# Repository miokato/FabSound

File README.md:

# FabSound
## This repository is created for people who want to make easy sound system using Arduino by yourself.

1. Amplifire
2. Speaker
3. Synthesizer

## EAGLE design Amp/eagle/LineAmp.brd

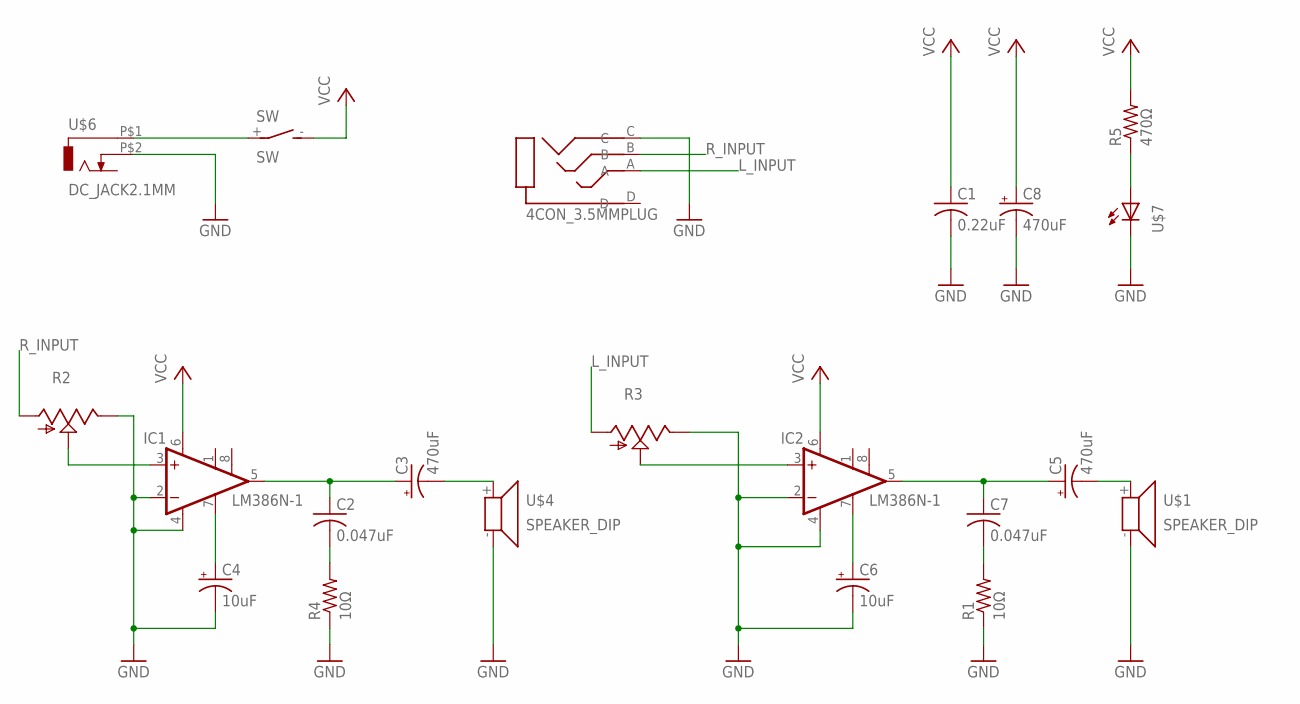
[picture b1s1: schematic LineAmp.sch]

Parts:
C1: 0.22uF; C075-042X103
C2, C7: 0.047uF; C050-024X044
C3, C5, C8: 470uF; E7,5-16
C4, C6: 10uF; E2-5
IC1, IC2: LM386N-1; DIL08
R1, R4: 10Ω; M1206
R2, R3: TRIM_US-ALPS-PANEL; ALPS-POT-PANEL
R5: 470Ω; M1206
SW: SW; 2PIN_DIP
U$1, U$4: SPEAKER_DIP; 2PIN_DIP
U$5: 4CON_3.5MMPLUG; 4PIN_DIP
U$6: DC_JACK2.1MM
U$7: LED5MM; 5MM

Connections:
GND: C1.2, C4.-, C6.-, C8.-, IC1.2 (-IN), IC1.4 (GND), IC2.2 (-IN), IC2.4 (GND), R1.1, R2.P$1 (E), R3.P$1 (E), R4.1, U$1.-, U$4.-, U$5.C, U$6.P$2 (2), U$7.OUT (C)
L_INPUT: R3.P$3 (A), U$5.A
unnamed: IC2.3 (+IN), R3.P$2 (S)
unnamed: C4.+, IC1.7 (BYPASS)
unnamed: IC1.3 (+IN), R2.P$2 (S)
unnamed: C6.+, IC2.7 (BYPASS)
unnamed: C2.1, C3.+, IC1.5 (OUT)
unnamed: C3.-, U$4.+
unnamed: C5.+, C7.1, IC2.5 (OUT)
unnamed: C5.-, U$1.+
unnamed: C2.2, R4.2
unnamed: C7.2, R1.2
unnamed: R5.1, U$7.IN (A)
unnamed: SW.+, U$6.P$1 (1)
R_INPUT: R2.P$3 (A), U$5.B
VCC: C1.1, C8.+, IC1.6 (VS), IC2.6 (VS), R5.2, SW.- (S)

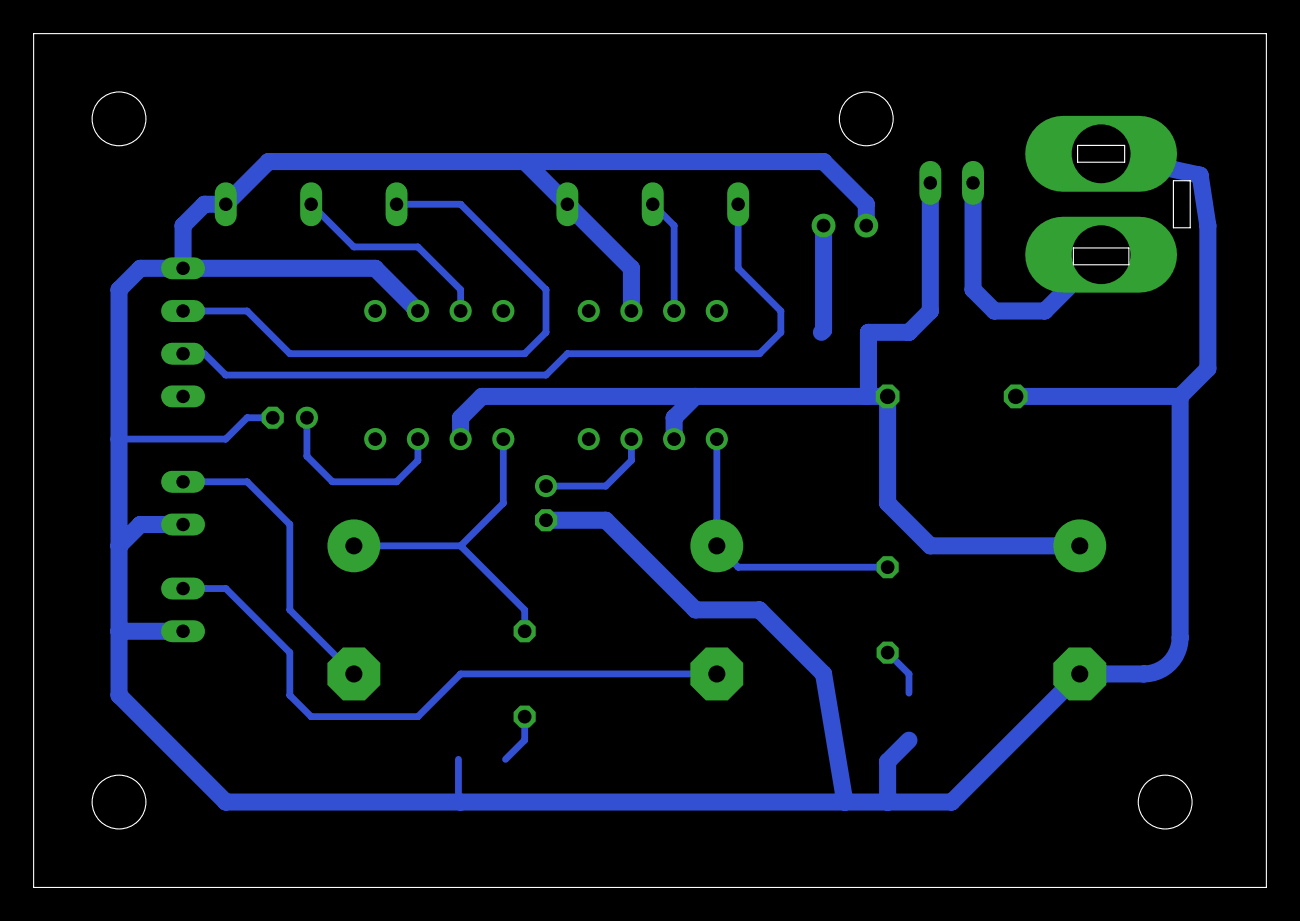
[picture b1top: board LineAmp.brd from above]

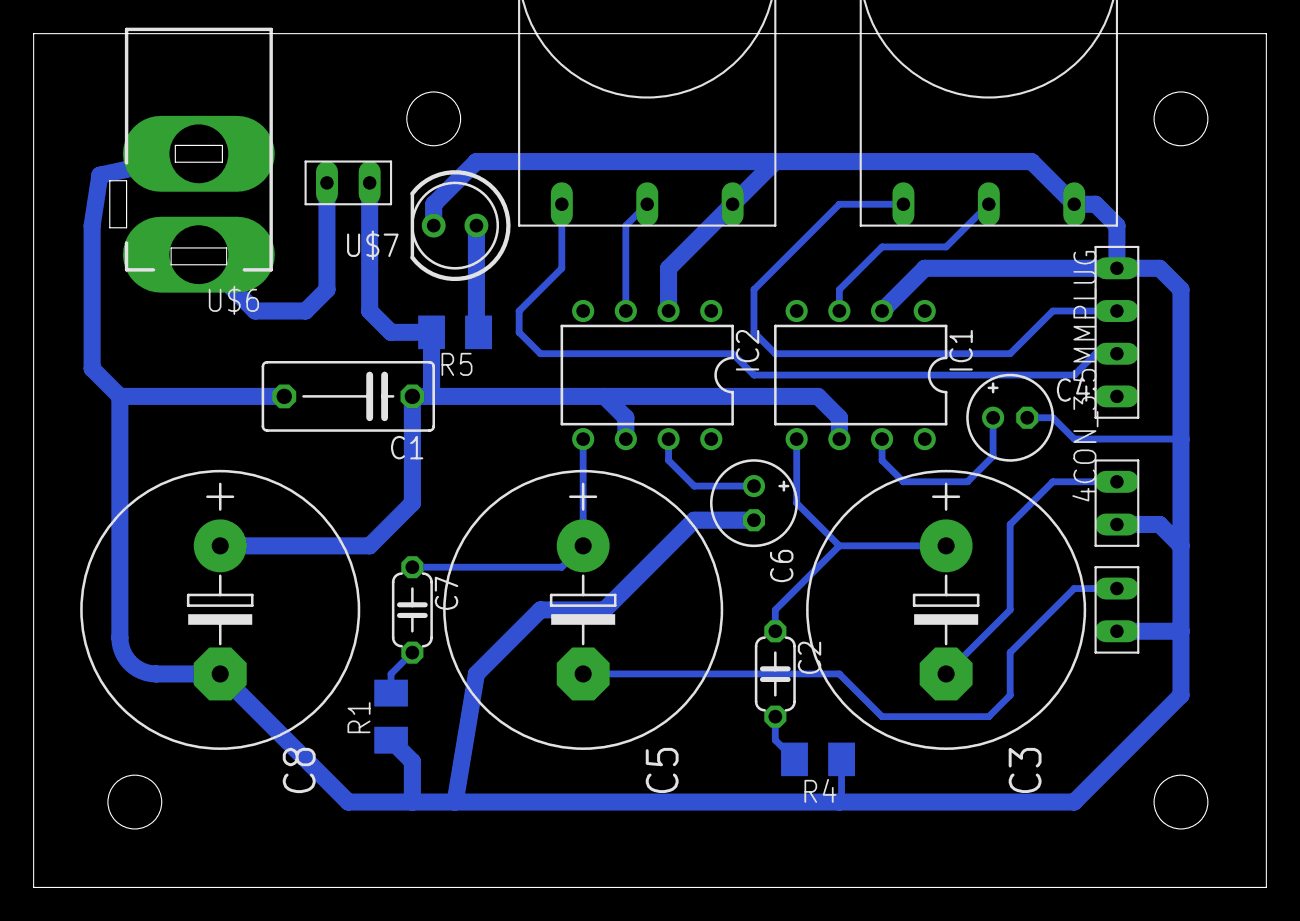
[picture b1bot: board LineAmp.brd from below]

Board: 2 copper layers, 73.3 x 50.8 mm, 21 parts (21 on the bottom side), 16 nets.

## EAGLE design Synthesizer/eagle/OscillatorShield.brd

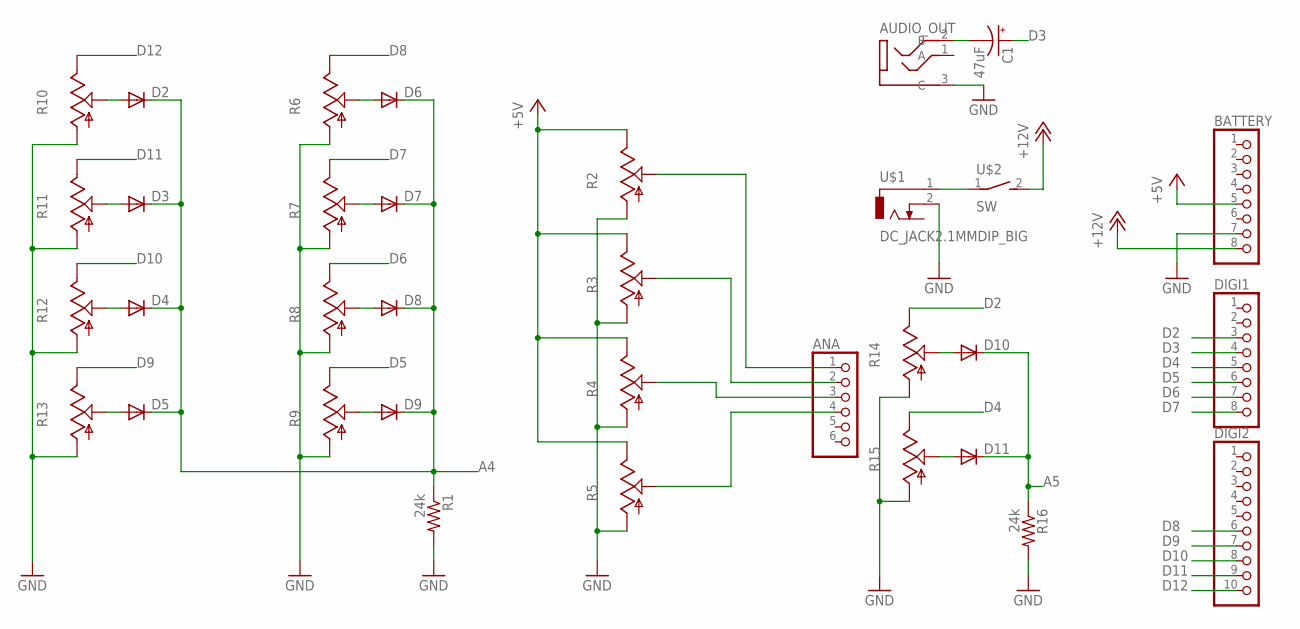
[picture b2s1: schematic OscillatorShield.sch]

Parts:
ANA: PINHD-1X6; 1X06
AUDIO_OUT: 3CON_3.5MMPLUG; 3PIN_DIP
BATTERY: PINHD-1X8; 1X08
C1: 47uF; E2,5-6
D2, D3, D4, D5, D6, D7, D8, D9, D10, D11: DIODE-SOD123; SOD123
DIGI1: PINHD-1X8; 1X08
DIGI2: PINHD-1X10; 1X10
R1, R16: 24k; R1206
R2, R3, R4, R5, R6, R7, R8, R9, R10, R11, R12, R13, R14, R15: TRIM_US-RJ9W; RJ9W
U$1: DC_JACK2.1MMDIP_BIG; 2PIN_DIP_BIG
U$2: SW; 2PIN_DIP_BIG

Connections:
+5V: BATTERY.5, R2.E, R3.E, R4.E, R5.E
+12V: BATTERY.8, U$2.2 (S)
A4: D2.C, D3.C, D4.C, D5.C, D6.C, D7.C, D8.C, D9.C, R1.1
A5: D10.C, D11.C, R16.1
D2: DIGI1.3, R14.E
D3: C1.+, DIGI1.4
D4: DIGI1.5, R15.E
D5: DIGI1.6, R9.E
D6: DIGI1.7, R8.E
D7: DIGI1.8, R7.E
D8: DIGI2.6, R6.E
D9: DIGI2.7, R13.E
D10: DIGI2.8, R12.E
D11: DIGI2.9, R11.E
D12: DIGI2.10, R10.E
GND: AUDIO_OUT.3 (C), BATTERY.7, R1.2, R2.A, R3.A, R4.A, R5.A, R6.A, R7.A, R8.A, R9.A, R10.A, R11.A, R12.A, R13.A, R14.A, R15.A, R16.2, U$1.2
unnamed: ANA.1, R2.S
unnamed: ANA.2, R3.S
unnamed: ANA.3, R4.S
unnamed: ANA.4, R5.S
unnamed: D2.A, R10.S
unnamed: D3.A, R11.S
unnamed: D4.A, R12.S
unnamed: D5.A, R13.S
unnamed: D9.A, R9.S
unnamed: D8.A, R8.S
unnamed: D7.A, R7.S
unnamed: D6.A, R6.S
unnamed: AUDIO_OUT.2 (B), C1.-
unnamed: U$1.1, U$2.1
unnamed: D11.A, R15.S
unnamed: D10.A, R14.S

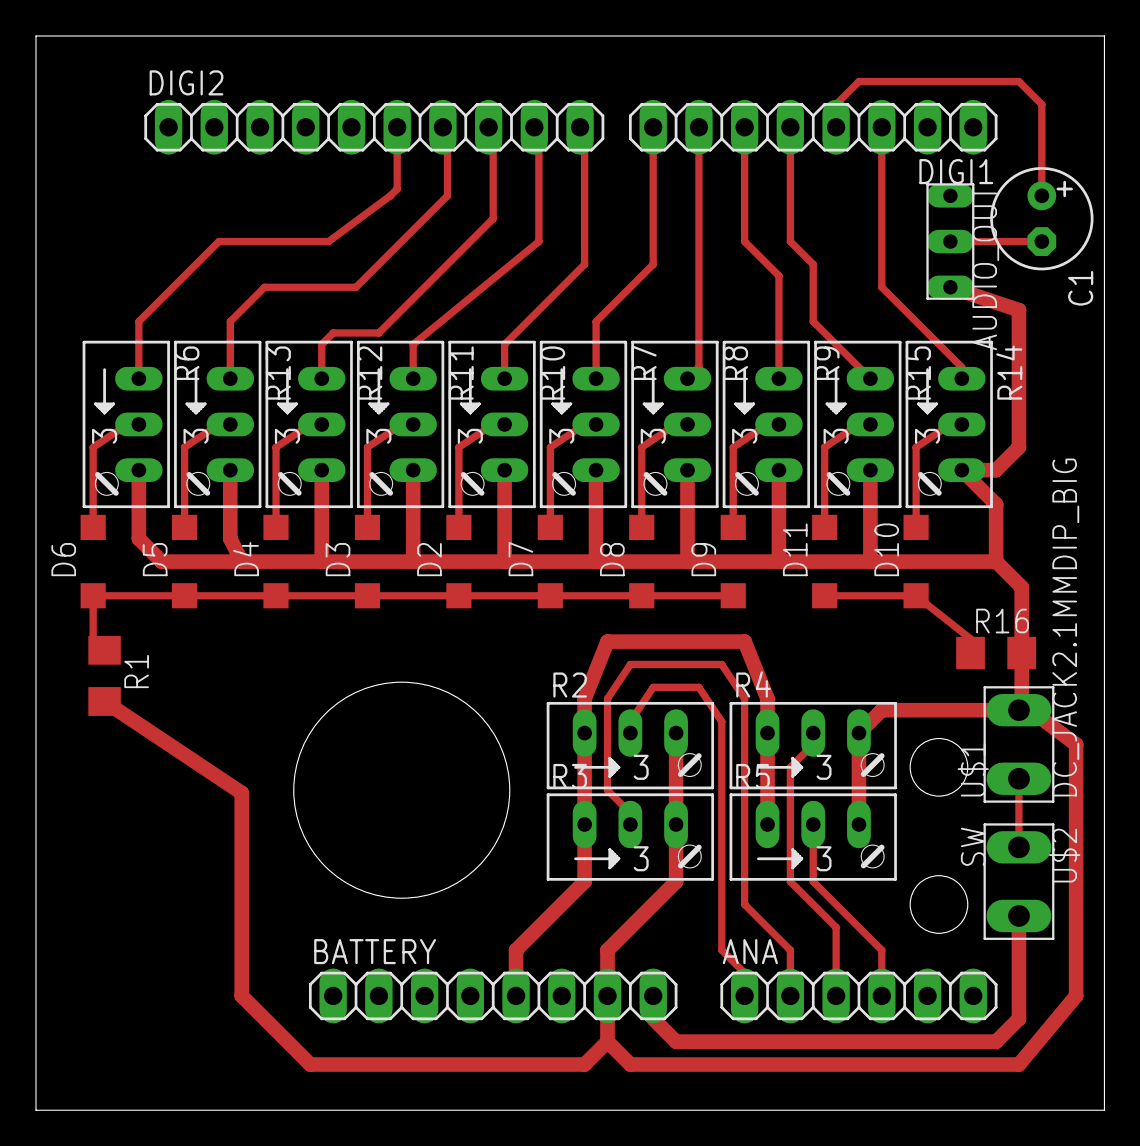
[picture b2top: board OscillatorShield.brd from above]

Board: 2 copper layers, 59.4 x 59.7 mm, 34 parts (0 on the bottom side), 32 nets.
